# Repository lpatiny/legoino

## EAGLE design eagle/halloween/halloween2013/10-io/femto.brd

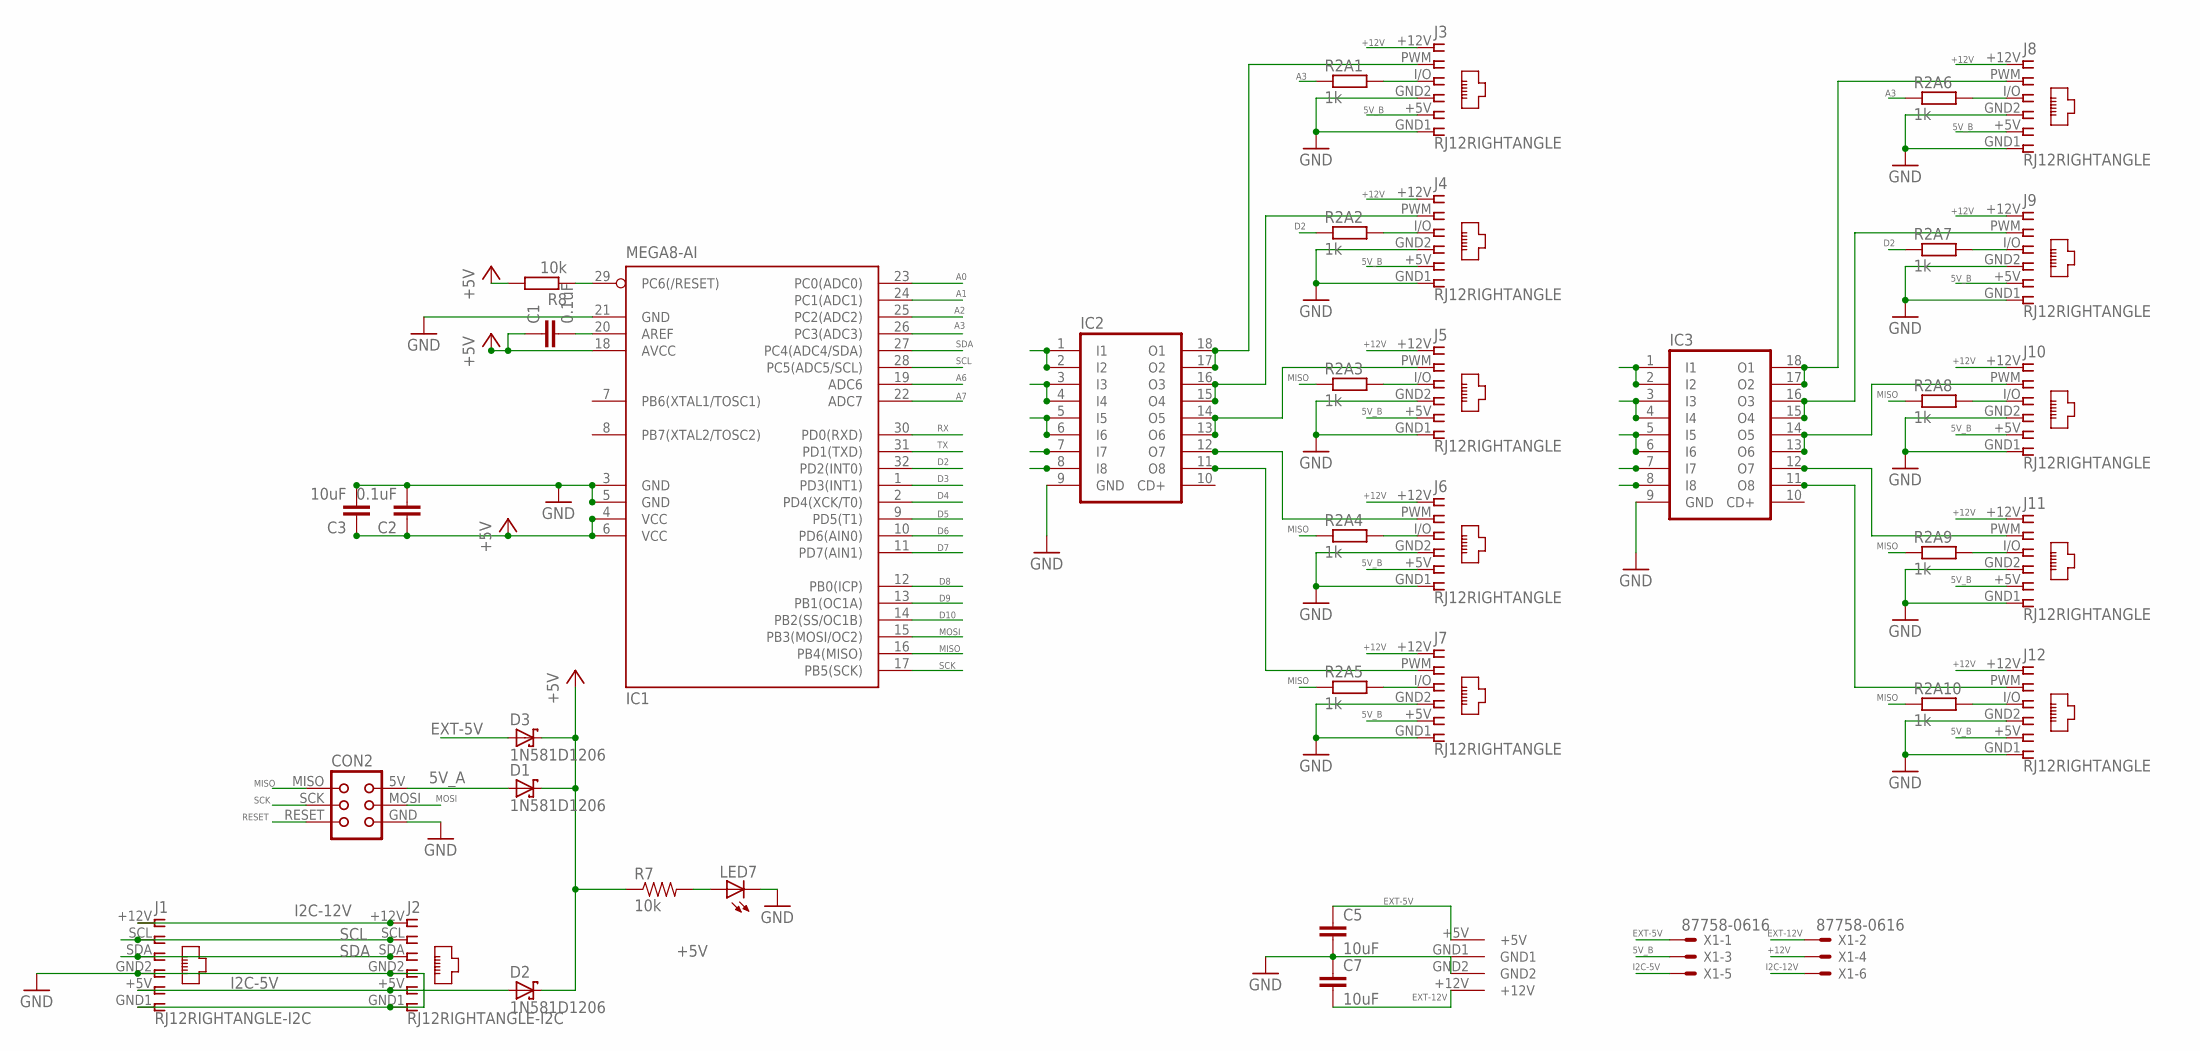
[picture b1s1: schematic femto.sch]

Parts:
C1, C2: 0.1uF; C1206
C3, C5, C7: 10uF; C1206
CON2: TINYISPTAG; TC2030-MCP
D1, D2, D3: 1N581D1206; LED-1206
IC1: MEGA8-AI; TQFP32-08
IC2, IC3: ULN2803A; SO18W
J1, J2: RJ12RIGHTANGLE-I2C; RJ12-RIGHTANGLE-I2C
J3, J4, J5, J6, J7, J8, J9, J10, J11, J12: RJ12RIGHTANGLE; RJ12-RIGHTANGLE
LED7: LEDCHIP-LED0603; CHIP-LED0603
R2A1, R2A2, R2A3, R2A4, R2A5, R2A6, R2A7, R2A8, R2A9, R2A10: 1k; M1206
R7: 10k; 0603-RES
R8: 10k; M1206
U$1: KPJX-4S-S
X1: 87758-0616

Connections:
5V_A: CON2.5V (VCC), D1.A
5V_B: J3.+5V (5), J4.+5V (5), J5.+5V (5), J6.+5V (5), J7.+5V (5), J8.+5V (5), J9.+5V (5), J10.+5V (5), J11.+5V (5), J12.+5V (5), X1.3
+5V: C1.1, C2.1, C3.1, D1.C, D2.C, D3.C, IC1.4 (VCC), IC1.6 (VCC), IC1.18 (AVCC), R7.1, R8.2
+12V: J3.+12V (1), J4.+12V (1), J5.+12V (1), J6.+12V (1), J7.+12V (1), J8.+12V (1), J9.+12V (1), J10.+12V (1), J11.+12V (1), J12.+12V (1), X1.4
A0: IC1.23 (PC0(ADC0))
A1: IC1.24 (PC1(ADC1))
A2: IC1.25 (PC2(ADC2))
A3: IC1.26 (PC3(ADC3)), R2A1.1, R2A6.1
A6: IC1.19 (ADC6)
A7: IC1.22 (ADC7)
D2: IC1.32 (PD2(INT0)), R2A2.1, R2A7.1
D3: IC1.1 (PD3(INT1))
D4: IC1.2 (PD4(XCK/T0))
D5: IC1.9 (PD5(T1))
D6: IC1.10 (PD6(AIN0))
D7: IC1.11 (PD7(AIN1))
D8: IC1.12 (PB0(ICP))
D9: IC1.13 (PB1(OC1A))
D10: IC1.14 (PB2(SS/OC1B))
EXT-5V: C5.1, D3.A, U$1.+5V, X1.1
EXT-12V: C7.2, U$1.+12V, X1.2
GND: C2.2, C3.2, C5.2, C7.1, CON2.GND, IC1.3 (GND), IC1.5 (GND), IC1.21 (GND), IC2.9 (GND), IC3.9 (GND), J1.GND1 (6), J1.GND2 (4), J2.GND1 (6), J2.GND2 (4), J3.GND1 (6), J3.GND2 (4), J4.GND1 (6), J4.GND2 (4), J5.GND1 (6), J5.GND2 (4), J6.GND1 (6), J6.GND2 (4), J7.GND1 (6), J7.GND2 (4), J8.GND1 (6), J8.GND2 (4), J9.GND1 (6), J9.GND2 (4), J10.GND1 (6), J10.GND2 (4), J11.GND1 (6), J11.GND2 (4), J12.GND1 (6), J12.GND2 (4), LED7.C, U$1.GND1, U$1.GND2
I2C-5V: D2.A, J1.+5V (5), J2.+5V (5), X1.5
I2C-12V: J1.+12V (1), J2.+12V (1), X1.6
MISO: CON2.MISO, IC1.16 (PB4(MISO)), R2A3.1, R2A4.1, R2A5.1, R2A8.1, R2A9.1, R2A10.1
MOSI: CON2.MOSI, IC1.15 (PB3(MOSI/OC2))
unnamed: IC2.1 (I1), IC2.2 (I2)
unnamed: J3.I/O (3), R2A1.2
unnamed: IC2.17 (O2), IC2.18 (O1), J3.PWM (2)
unnamed: C1.2, IC1.20 (AREF)
unnamed: IC2.15 (O4), IC2.16 (O3), J4.PWM (2)
unnamed: IC2.13 (O6), IC2.14 (O5), J5.PWM (2)
unnamed: IC2.3 (I3), IC2.4 (I4)
unnamed: IC2.5 (I5), IC2.6 (I6)
unnamed: J4.I/O (3), R2A2.2
unnamed: J5.I/O (3), R2A3.2
unnamed: IC2.12 (O7), J6.PWM (2)
unnamed: J6.I/O (3), R2A4.2
unnamed: IC2.11 (O8), J7.PWM (2)
unnamed: J7.I/O (3), R2A5.2
unnamed: LED7.A, R7.2
unnamed: IC3.17 (O2), IC3.18 (O1), J8.PWM (2)
unnamed: IC3.15 (O4), IC3.16 (O3), J9.PWM (2)
unnamed: IC3.13 (O6), IC3.14 (O5), J10.PWM (2)
unnamed: J8.I/O (3), R2A6.2
unnamed: J9.I/O (3), R2A7.2
unnamed: J10.I/O (3), R2A8.2
unnamed: IC3.12 (O7), J11.PWM (2)
unnamed: J11.I/O (3), R2A9.2
unnamed: IC3.11 (O8), J12.PWM (2)
unnamed: J12.I/O (3), R2A10.2
unnamed: IC3.1 (I1), IC3.2 (I2)
unnamed: IC3.3 (I3), IC3.4 (I4)
unnamed: IC3.5 (I5), IC3.6 (I6)
RESET: CON2.RESET, IC1.29 (PC6(/RESET)), R8.1
RX: IC1.30 (PD0(RXD))
SCK: CON2.SCK, IC1.17 (PB5(SCK))
SCL: IC1.28 (PC5(ADC5/SCL)), J1.SCL (2), J2.SCL (2)
SDA: IC1.27 (PC4(ADC4/SDA)), J1.SDA (3), J2.SDA (3)
TX: IC1.31 (PD1(TXD))

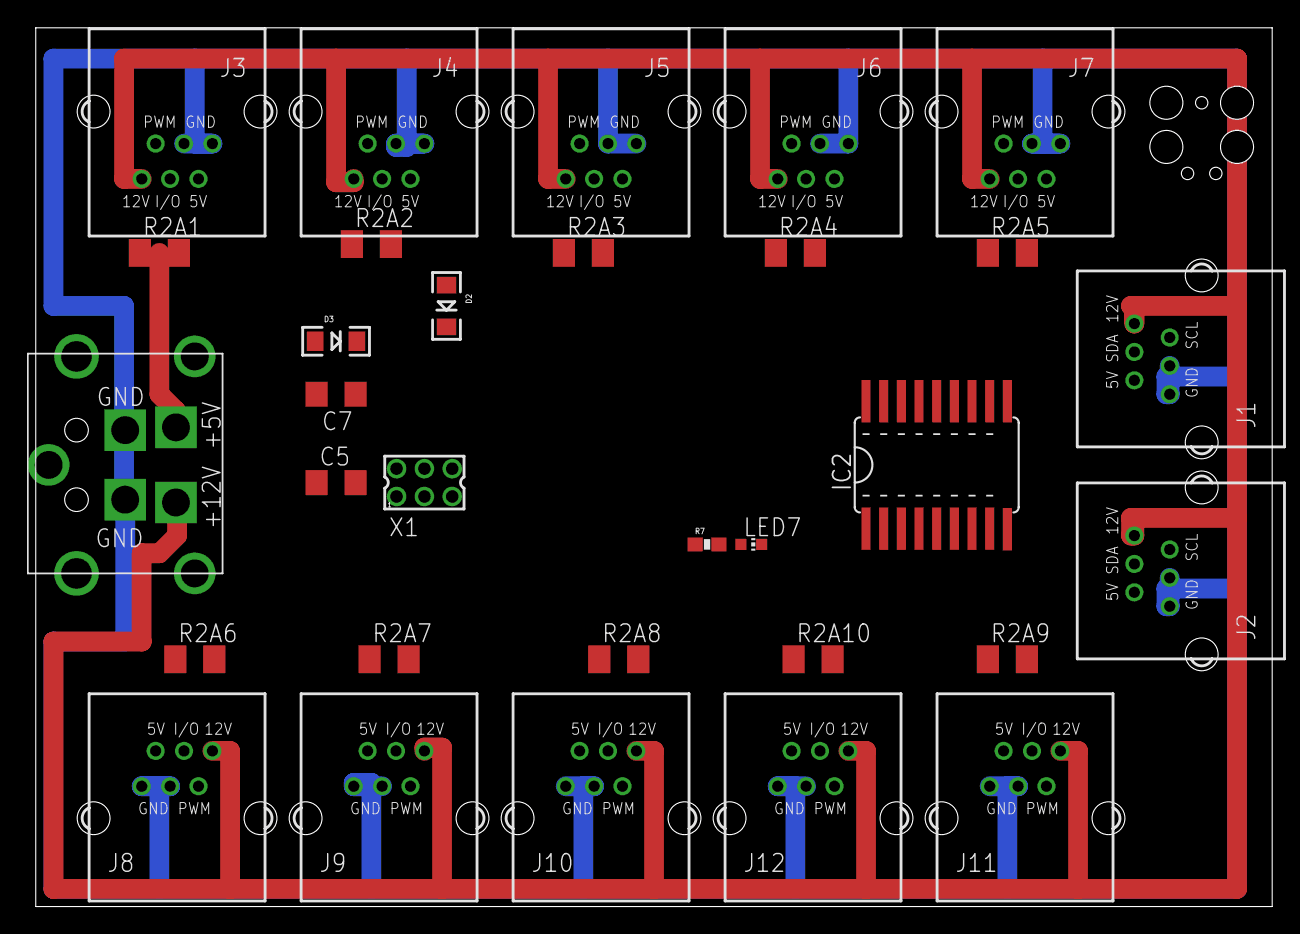
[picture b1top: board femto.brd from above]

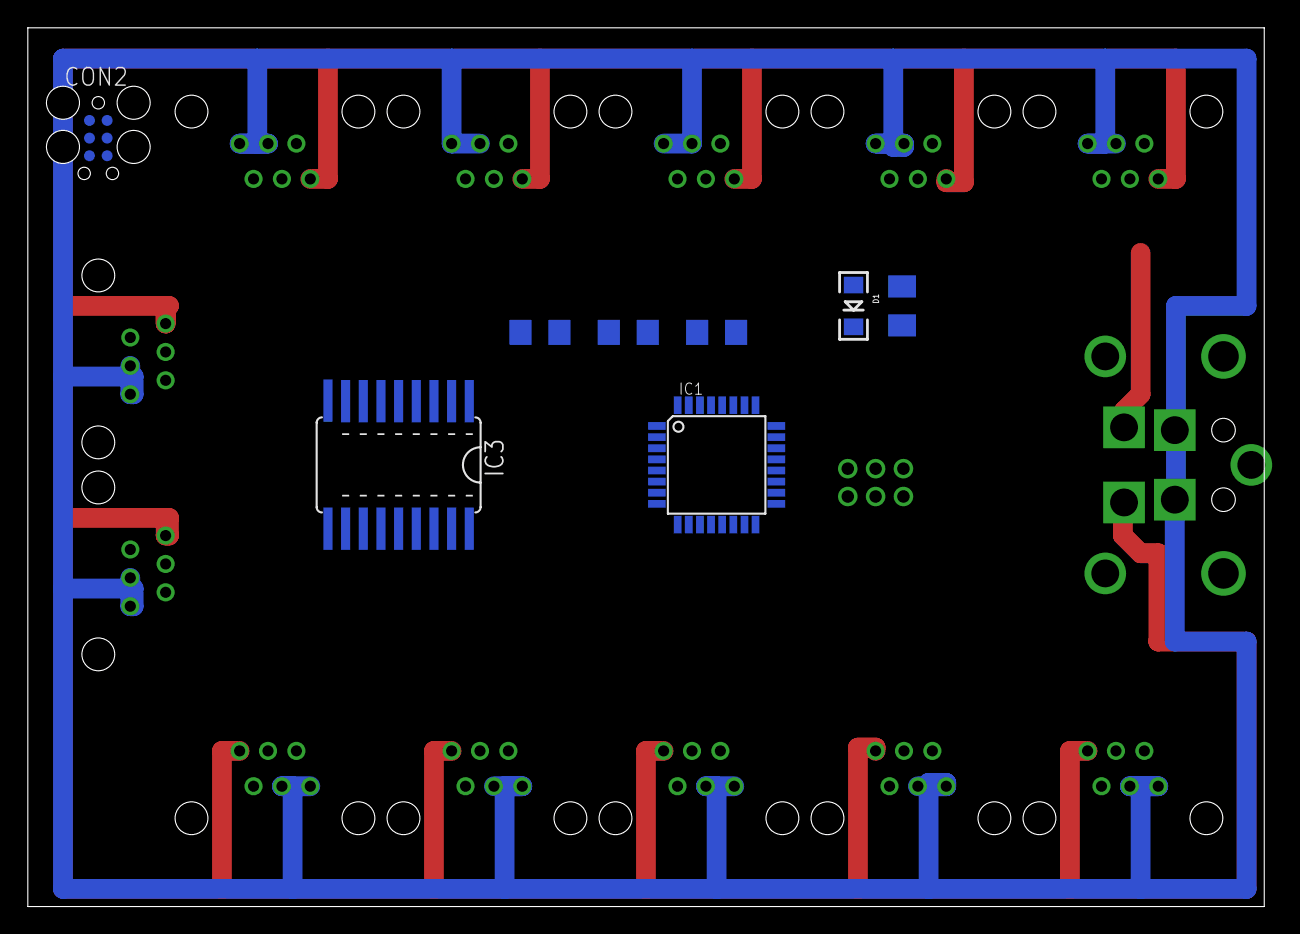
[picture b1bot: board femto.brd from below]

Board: 2 copper layers, 88.9 x 63.2 mm, 39 parts (8 on the bottom side), 45 nets.

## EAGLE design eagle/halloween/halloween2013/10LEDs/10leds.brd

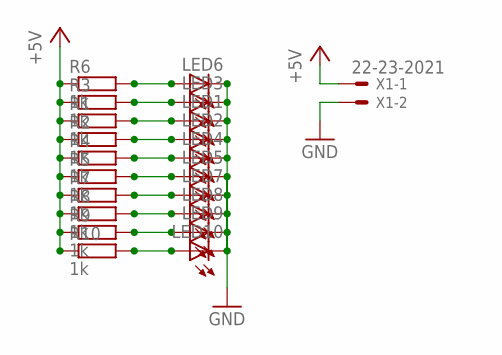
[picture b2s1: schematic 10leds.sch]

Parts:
LED1, LED2, LED3, LED4, LED5, LED6, LED7, LED8, LED9, LED10: LED3MM
R1, R2, R3, R4, R5, R6, R7, R8, R9, R10: 1k; M1206
X1: 22-23-2021

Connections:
+5V: R1.1, R2.1, R3.1, R4.1, R5.1, R6.1, R7.1, R8.1, R9.1, R10.1, X1.1
GND: LED1.K (C), LED2.K (C), LED3.K (C), LED4.K (C), LED5.K (C), LED6.K (C), LED7.K (C), LED8.K (C), LED9.K (C), LED10.K (C), X1.2
unnamed: LED1.A, R1.2
unnamed: LED2.A, R2.2
unnamed: LED4.A, R4.2
unnamed: LED5.A, R5.2
unnamed: LED7.A, R7.2
unnamed: LED8.A, R8.2
unnamed: LED9.A, R9.2
unnamed: LED10.A, R10.2
unnamed: LED3.A, R3.2
unnamed: LED6.A, R6.2

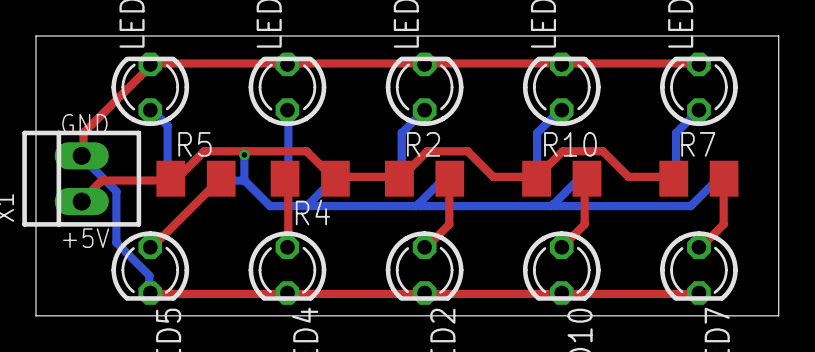
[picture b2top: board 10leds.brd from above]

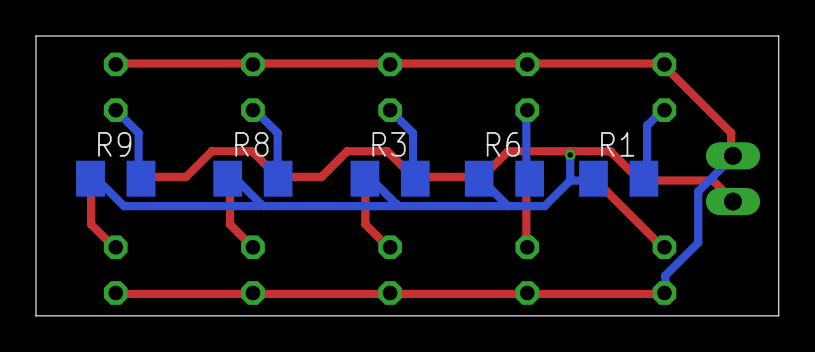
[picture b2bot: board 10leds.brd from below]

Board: 2 copper layers, 41.3 x 15.5 mm, 21 parts (5 on the bottom side), 12 nets.

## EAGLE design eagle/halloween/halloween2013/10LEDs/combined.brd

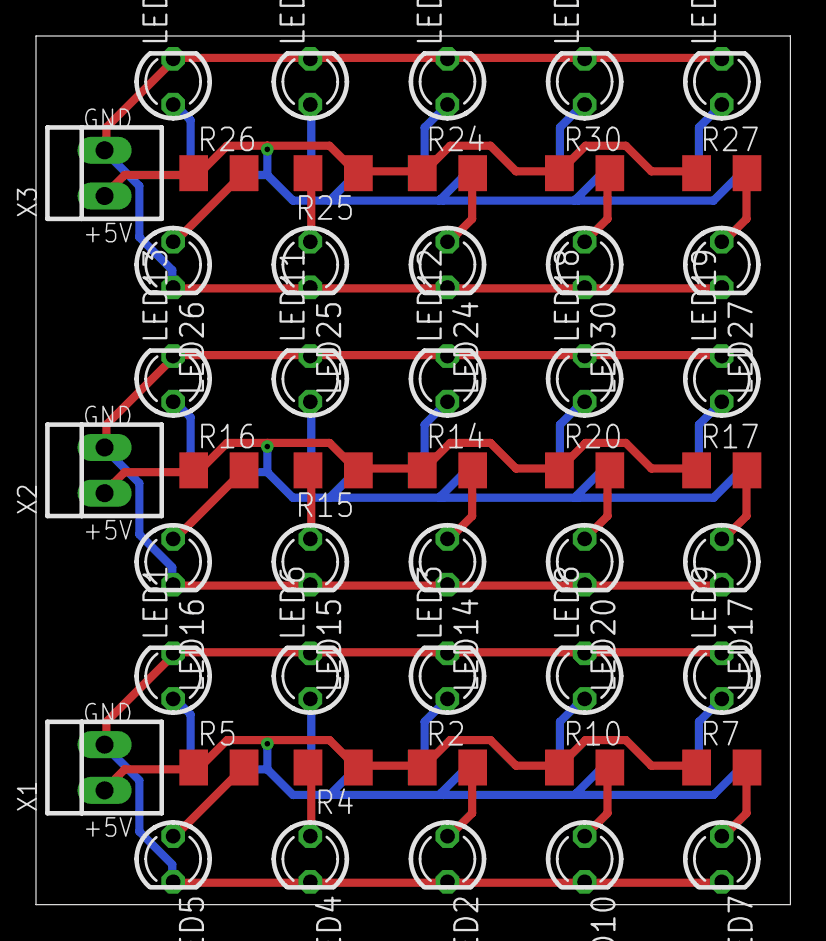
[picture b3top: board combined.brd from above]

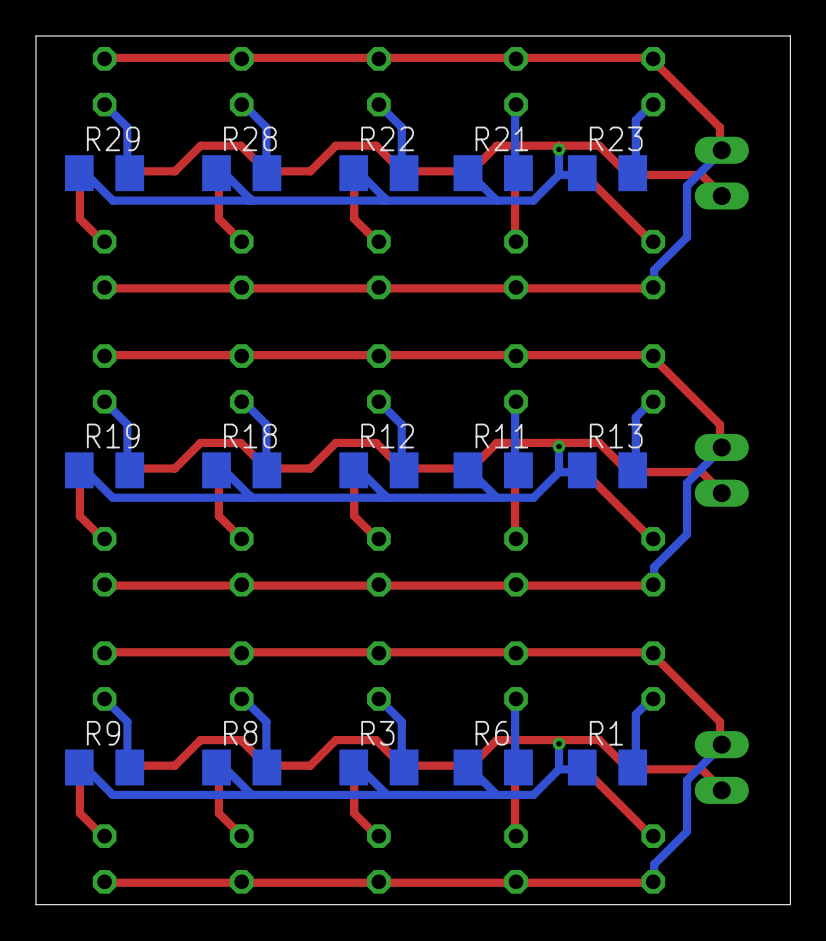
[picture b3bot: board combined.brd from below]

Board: 2 copper layers, 41.9 x 48.3 mm, 63 parts (15 on the bottom side), 36 nets.

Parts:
LED1, LED2, LED3, LED4, LED5, LED6, LED7, LED8, LED9, LED10, LED11, LED12, LED13, LED14, LED15, LED16, LED17, LED18, LED19, LED20, LED21, LED22, LED23, LED24, LED25, LED26, LED27, LED28, LED29, LED30: LED3MM
R1, R2, R3, R4, R5, R6, R7, R8, R9, R10, R11, R12, R13, R14, R15, R16, R17, R18, R19, R20, R21, R22, R23, R24, R25, R26, R27, R28, R29, R30: 1k; M1206
X1, X2, X3: 22-23-2021

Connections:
+5V: R1.1, R2.1, R3.1, R4.1, R5.1, R6.1, R7.1, R8.1, R9.1, R10.1, X1.1
+5V1: R11.1, R12.1, R13.1, R14.1, R15.1, R16.1, R17.1, R18.1, R19.1, R20.1, X2.1
+5V2: R21.1, R22.1, R23.1, R24.1, R25.1, R26.1, R27.1, R28.1, R29.1, R30.1, X3.1
GND: LED1.K, LED2.K, LED3.K, LED4.K, LED5.K, LED6.K, LED7.K, LED8.K, LED9.K, LED10.K, X1.2
GND1: LED11.K, LED12.K, LED13.K, LED14.K, LED15.K, LED16.K, LED17.K, LED18.K, LED19.K, LED20.K, X2.2
GND2: LED21.K, LED22.K, LED23.K, LED24.K, LED25.K, LED26.K, LED27.K, LED28.K, LED29.K, LED30.K, X3.2
unnamed: LED1.A, R1.2
unnamed: LED2.A, R2.2
unnamed: LED4.A, R4.2
unnamed: LED5.A, R5.2
unnamed: LED7.A, R7.2
unnamed: LED8.A, R8.2
unnamed: LED9.A, R9.2
unnamed: LED10.A, R10.2
unnamed: LED11.A, R11.2
unnamed: LED12.A, R12.2
unnamed: LED13.A, R13.2
unnamed: LED14.A, R14.2
unnamed: LED15.A, R15.2
unnamed: LED16.A, R16.2
unnamed: LED17.A, R17.2
unnamed: LED3.A, R3.2
unnamed: LED18.A, R18.2
unnamed: LED19.A, R19.2
unnamed: LED20.A, R20.2
unnamed: LED21.A, R21.2
unnamed: LED22.A, R22.2
unnamed: LED23.A, R23.2
unnamed: LED6.A, R6.2
unnamed: LED24.A, R24.2
unnamed: LED25.A, R25.2
unnamed: LED26.A, R26.2
unnamed: LED27.A, R27.2
unnamed: LED28.A, R28.2
unnamed: LED29.A, R29.2
unnamed: LED30.A, R30.2

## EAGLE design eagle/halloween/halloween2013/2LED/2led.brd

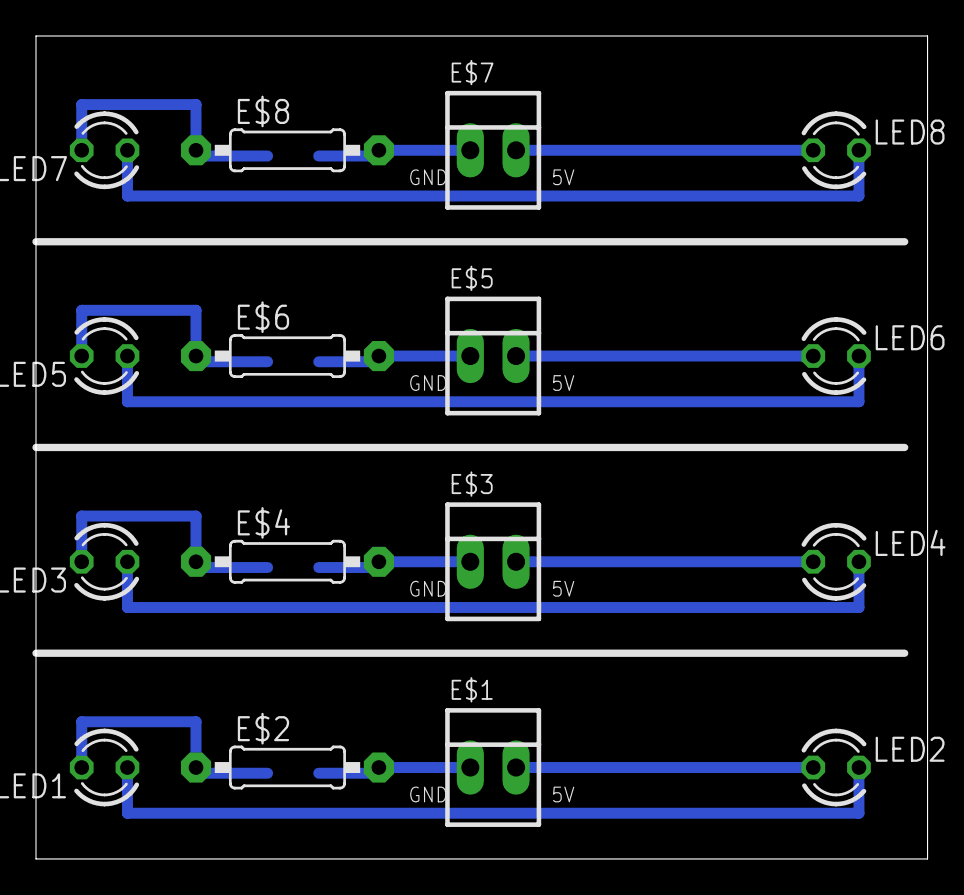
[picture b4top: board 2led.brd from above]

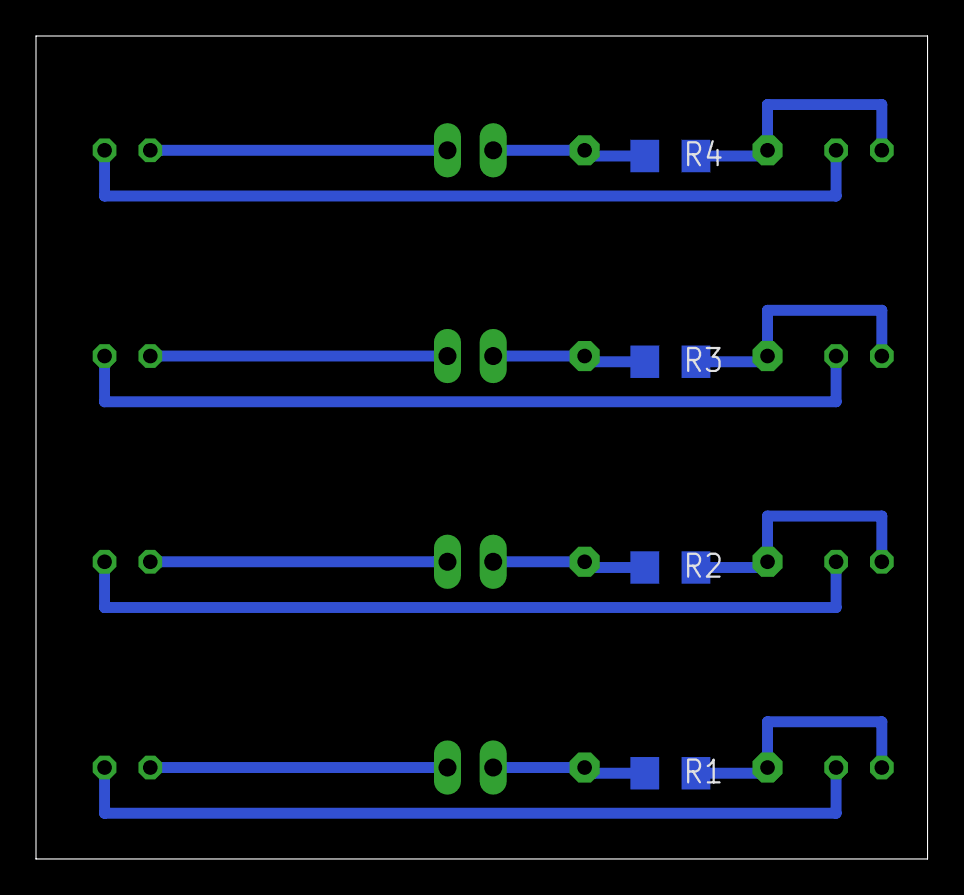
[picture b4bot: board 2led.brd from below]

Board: 2 copper layers, 49.5 x 45.7 mm, 20 parts (4 on the bottom side), 16 nets.

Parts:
E$1, E$3, E$5, E$7: 22-23-2021
E$2, E$4, E$6, E$8: 0207/10
LED1, LED2, LED3, LED4, LED5, LED6, LED7, LED8: LED3MM
R1, R2, R3, R4: 1K; R1206

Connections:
S$1: E$1.1, E$2.2, R1.1
S$2: E$3.1, E$4.2, R2.1
S$3: LED1.A, LED2.K
S$4: E$2.1, LED1.K, R1.2
S$5: E$1.2, LED2.A
S$6: E$3.2, LED4.A
S$7: E$4.1, LED3.K, R2.2
S$8: LED3.A, LED4.K
S$9: E$5.1, E$6.2, R3.1
S$10: E$5.2, LED6.A
S$11: E$6.1, LED5.K, R3.2
S$12: LED5.A, LED6.K
S$13: E$7.1, E$8.2, R4.1
S$14: E$7.2, LED8.A
S$15: E$8.1, LED7.K, R4.2
S$16: LED7.A, LED8.K

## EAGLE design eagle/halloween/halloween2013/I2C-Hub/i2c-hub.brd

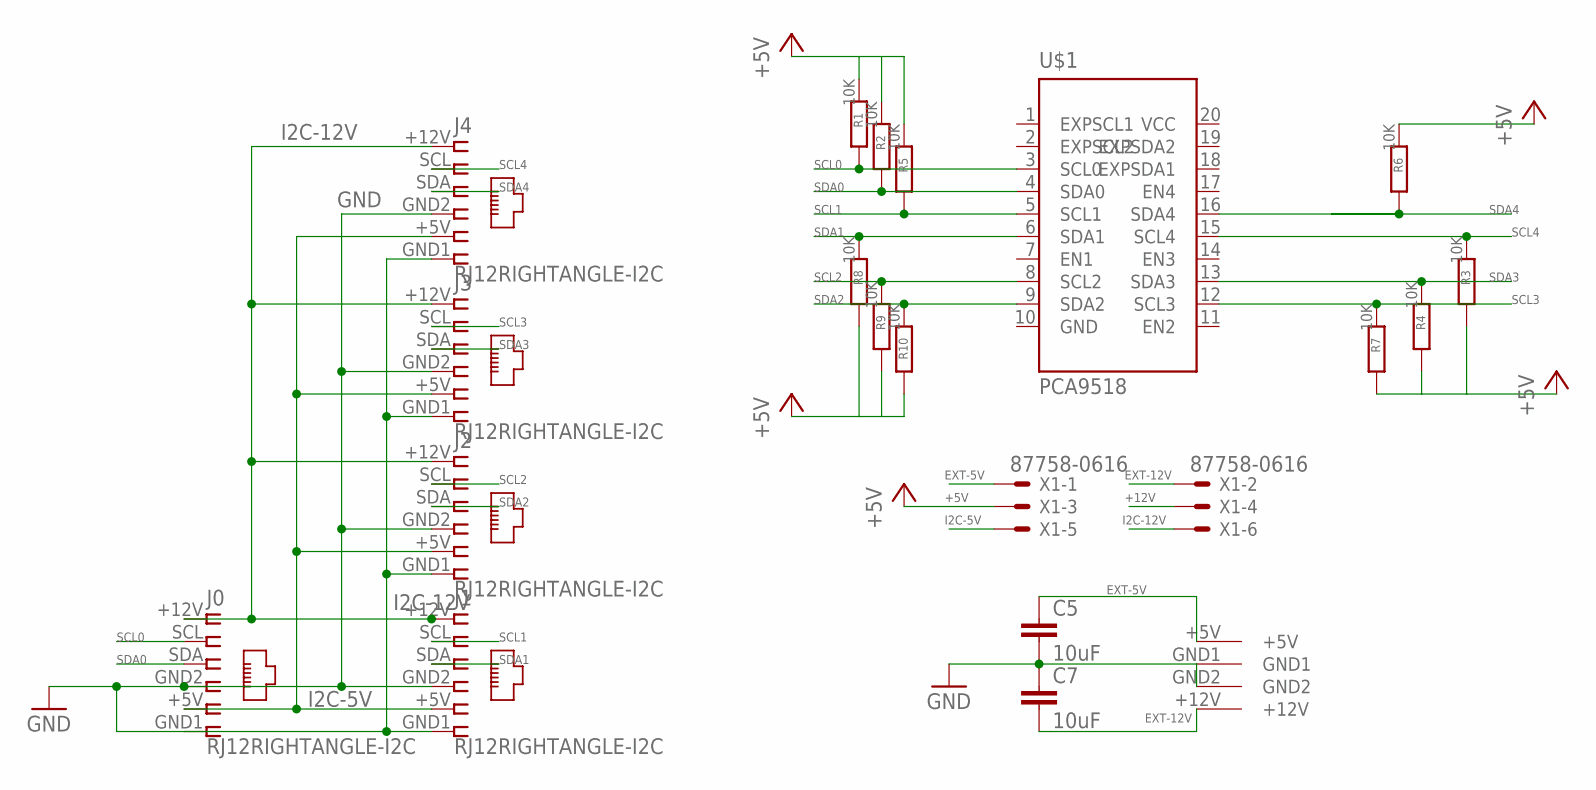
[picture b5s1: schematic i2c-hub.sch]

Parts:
C5, C7: 10uF; C1206
J0, J1, J2, J3, J4: RJ12RIGHTANGLE-I2C; RJ12-RIGHTANGLE-I2C
R1, R2, R3, R4, R5, R6, R7, R8, R9, R10: 10K; M1206
U$1: PCA9518; SO20W
U$2: KPJX-4S-S
X1: 87758-0616

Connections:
+5V: R1.1, R2.1, R3.2, R4.2, R5.1, R6.1, R7.2, R9.2, R10.2, X1.3
+12V: X1.4
EXT-5V: C5.1, U$2.+5V, X1.1
EXT-12V: C7.2, U$2.+12V, X1.2
GND: C5.2, C7.1, J0.GND1 (6), J0.GND2 (4), J1.GND1 (6), J1.GND2 (4), J2.GND1 (6), J2.GND2 (4), J3.GND1 (6), J3.GND2 (4), J4.GND1 (6), J4.GND2 (4), U$1.10 (GND), U$2.GND1, U$2.GND2
I2C-5V: J0.+5V (5), J1.+5V (5), J2.+5V (5), J3.+5V (5), J4.+5V (5), X1.5
I2C-12V: J0.+12V (1), J1.+12V (1), J2.+12V (1), J3.+12V (1), J4.+12V (1), X1.6
SCL0: J0.SCL (2), R1.2, U$1.3 (SCL0)
SCL1: J1.SCL (2), R5.2, U$1.5 (SCL1)
SCL2: J2.SCL (2), R9.1, U$1.8 (SCL2)
SCL3: J3.SCL (2), R7.1, U$1.12 (SCL3)
SCL4: J4.SCL (2), R3.1, U$1.15 (SCL4)
SDA0: J0.SDA (3), R2.2, U$1.4 (SDA0)
SDA1: J1.SDA (3), R8.1, U$1.6 (SDA1)
SDA2: J2.SDA (3), R10.1, U$1.9 (SDA2)
SDA3: J3.SDA (3), R4.1, U$1.13 (SDA3)
SDA4: J4.SDA (3), R6.2, U$1.16 (SDA4)
VCC: U$1.20 (VCC)

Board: 2 copper layers, 20 parts (0 on the bottom side), 16 nets, no tracks yet.

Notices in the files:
parts and their libraries:
lpatiny: ©2009 ROFA.cz - modified and updated by Robert Darlington ‹rdarlington@gmail.com›
SparkFun: Licensing: CC v3.0 Share-Alike You are welcome to use this library for commercial purposes.
